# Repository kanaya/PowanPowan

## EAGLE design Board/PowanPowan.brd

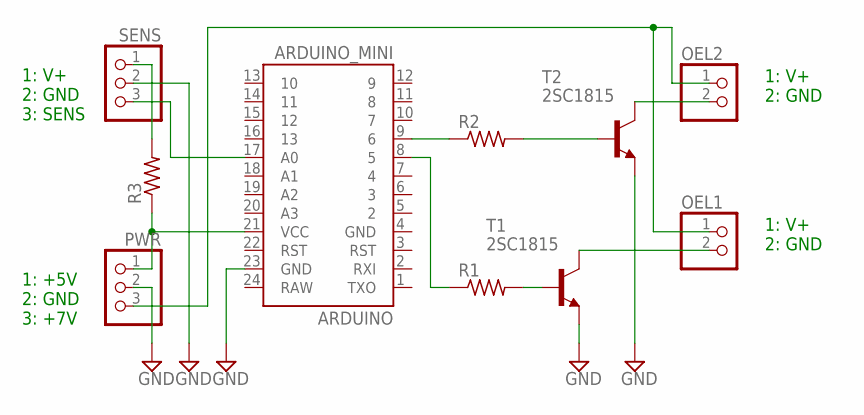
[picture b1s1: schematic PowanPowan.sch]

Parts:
ARDUINO: ARDUINO_MINI
OEL1, OEL2: PINHD-1X2; 1X02
PWR: PINHD-1X3; 1X03
R1, R2, R3: R-US_0204/7; 0204/7
SENS: PINHD-1X3; 1X03
T1, T2: 2SC1815; TO92-ECB

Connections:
GND: ARDUINO.23 (GND), PWR.2, SENS.2, T1.E, T2.E
unnamed: ARDUINO.8 (5), R1.1
unnamed: ARDUINO.9 (6), R2.1
unnamed: ARDUINO.21 (VCC), PWR.1, R3.1
unnamed: R2.2, T2.B
unnamed: R1.2, T1.B
unnamed: OEL1.2, T1.C
unnamed: OEL2.2, T2.C
unnamed: OEL1.1, OEL2.1, PWR.3
unnamed: R3.2, SENS.1
unnamed: ARDUINO.17 (A0), SENS.3

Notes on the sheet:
1: +5V 2: GND 3: +7V
1: V+ 2: GND
1: V+ 2: GND 3: SENS

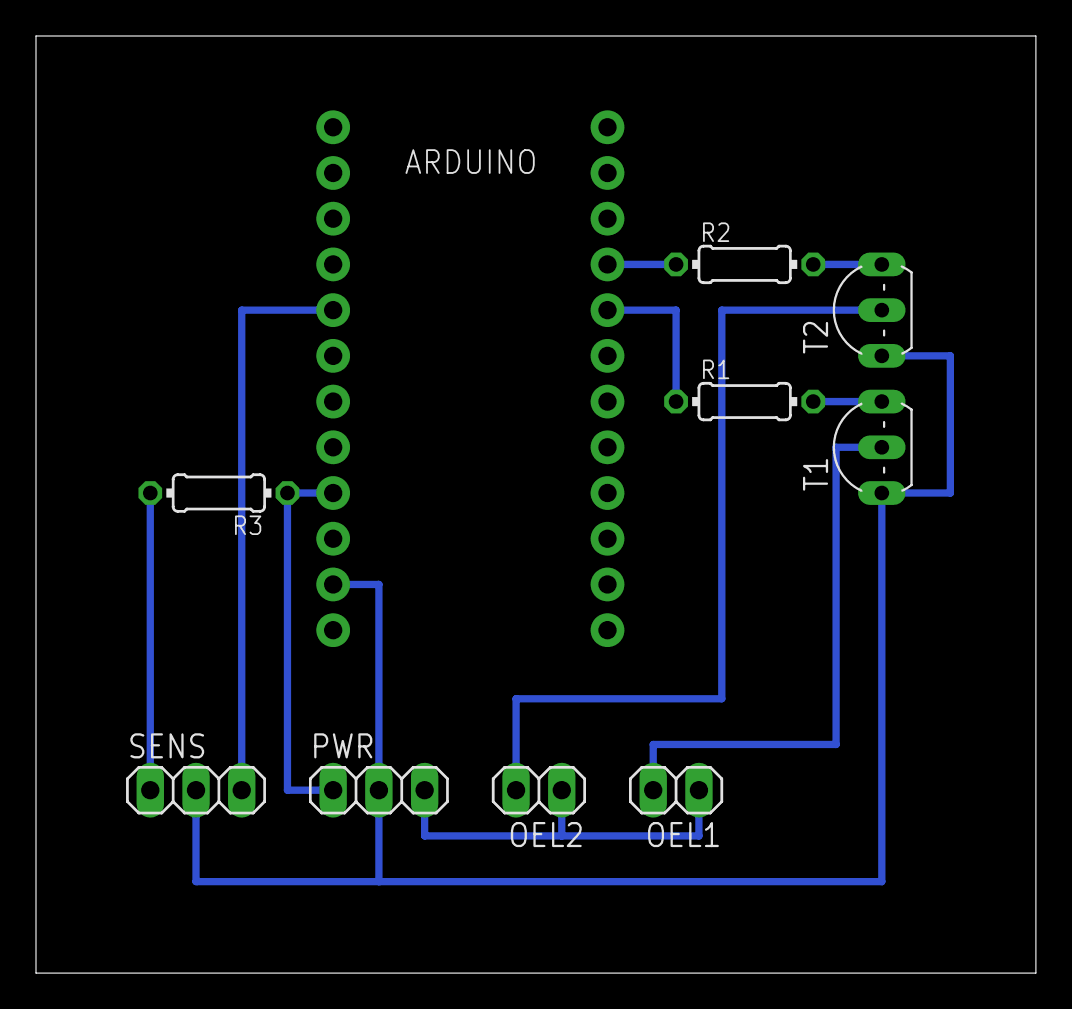
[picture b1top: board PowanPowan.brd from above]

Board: 2 copper layers, 55.5 x 52.1 mm, 10 parts (0 on the bottom side), 11 nets.

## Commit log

2014-12-11 Inital commit.

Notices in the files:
parts and their libraries:
SparkFun-Boards: Licensing: Creative Commons ShareAlike 4.0 International - https://creativecommons.org/licenses/by-sa/4.0
